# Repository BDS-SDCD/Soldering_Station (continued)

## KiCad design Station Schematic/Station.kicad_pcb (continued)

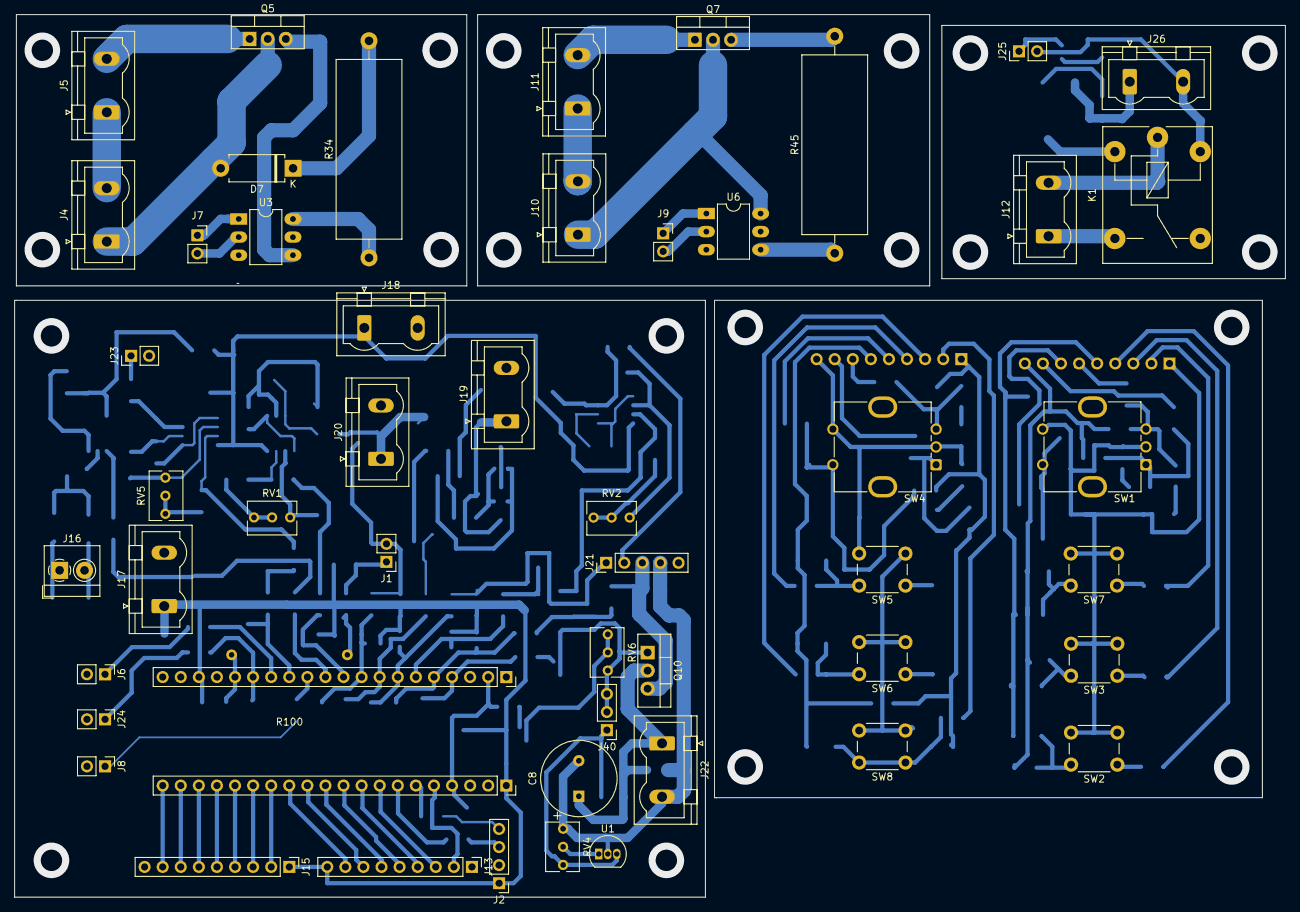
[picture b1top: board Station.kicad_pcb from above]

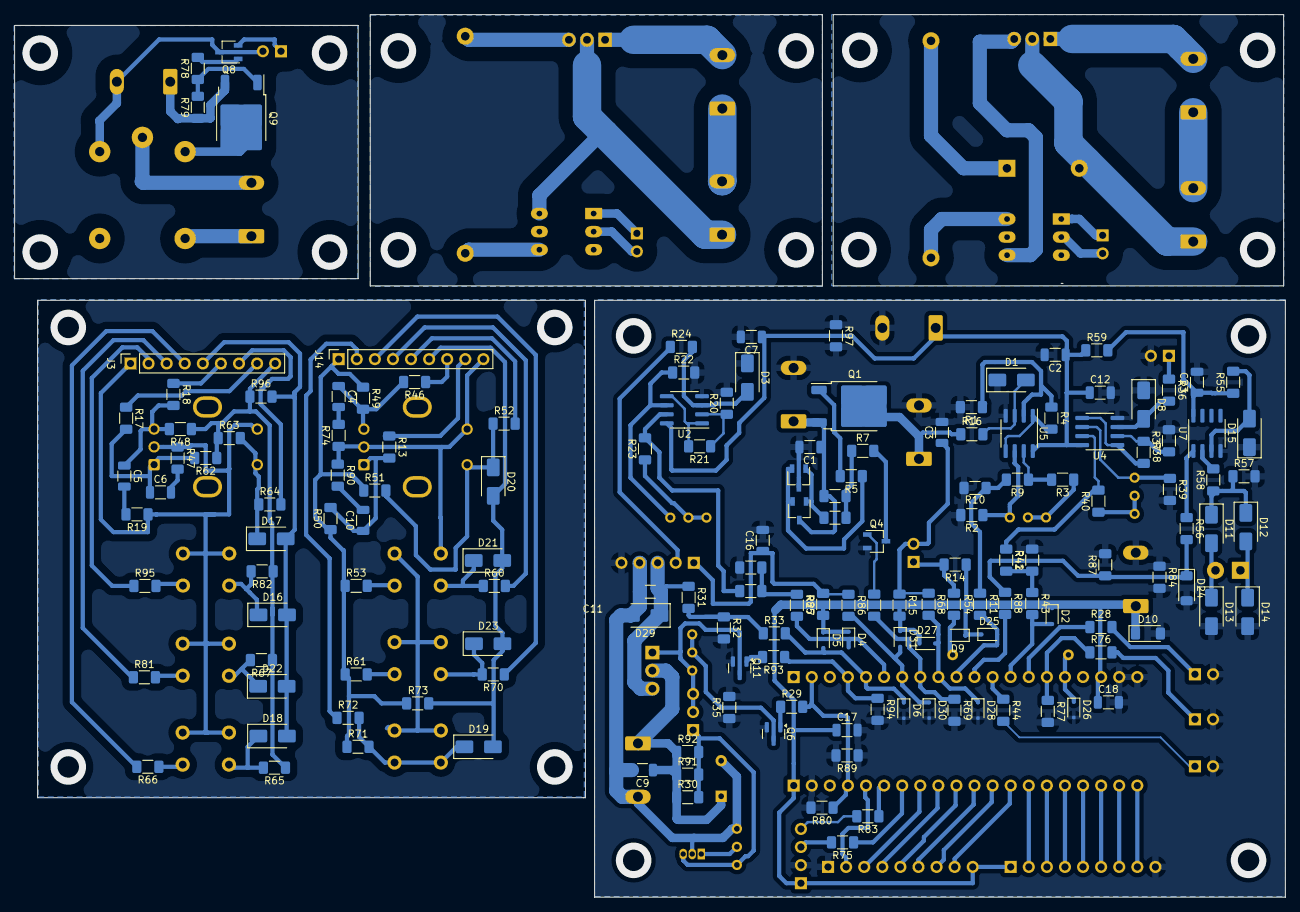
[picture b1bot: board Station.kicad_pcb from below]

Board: 2 copper layers, 178.5 x 124.0 mm, 205 parts (154 on the bottom side), 148 nets.

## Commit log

2024-12-13 Fixed critical bug. Did'n turn off PAC's Controll Unit Pin to state resset
2024-12-15 Add Button mode for Full Power button
2024-12-16 Incoder chenge
2025-04-12 alpha
2025-05-09 PAC was changed
2025-05-09 Update Readme.md
    PAC was changed
2025-05-11 Changed PAC frequency calculation.
